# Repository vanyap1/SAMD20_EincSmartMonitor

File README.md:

# SAMD20_EinkSmartMonitor
Atmel SAMD20E17 mcu based EINK smart monitor with LORA module

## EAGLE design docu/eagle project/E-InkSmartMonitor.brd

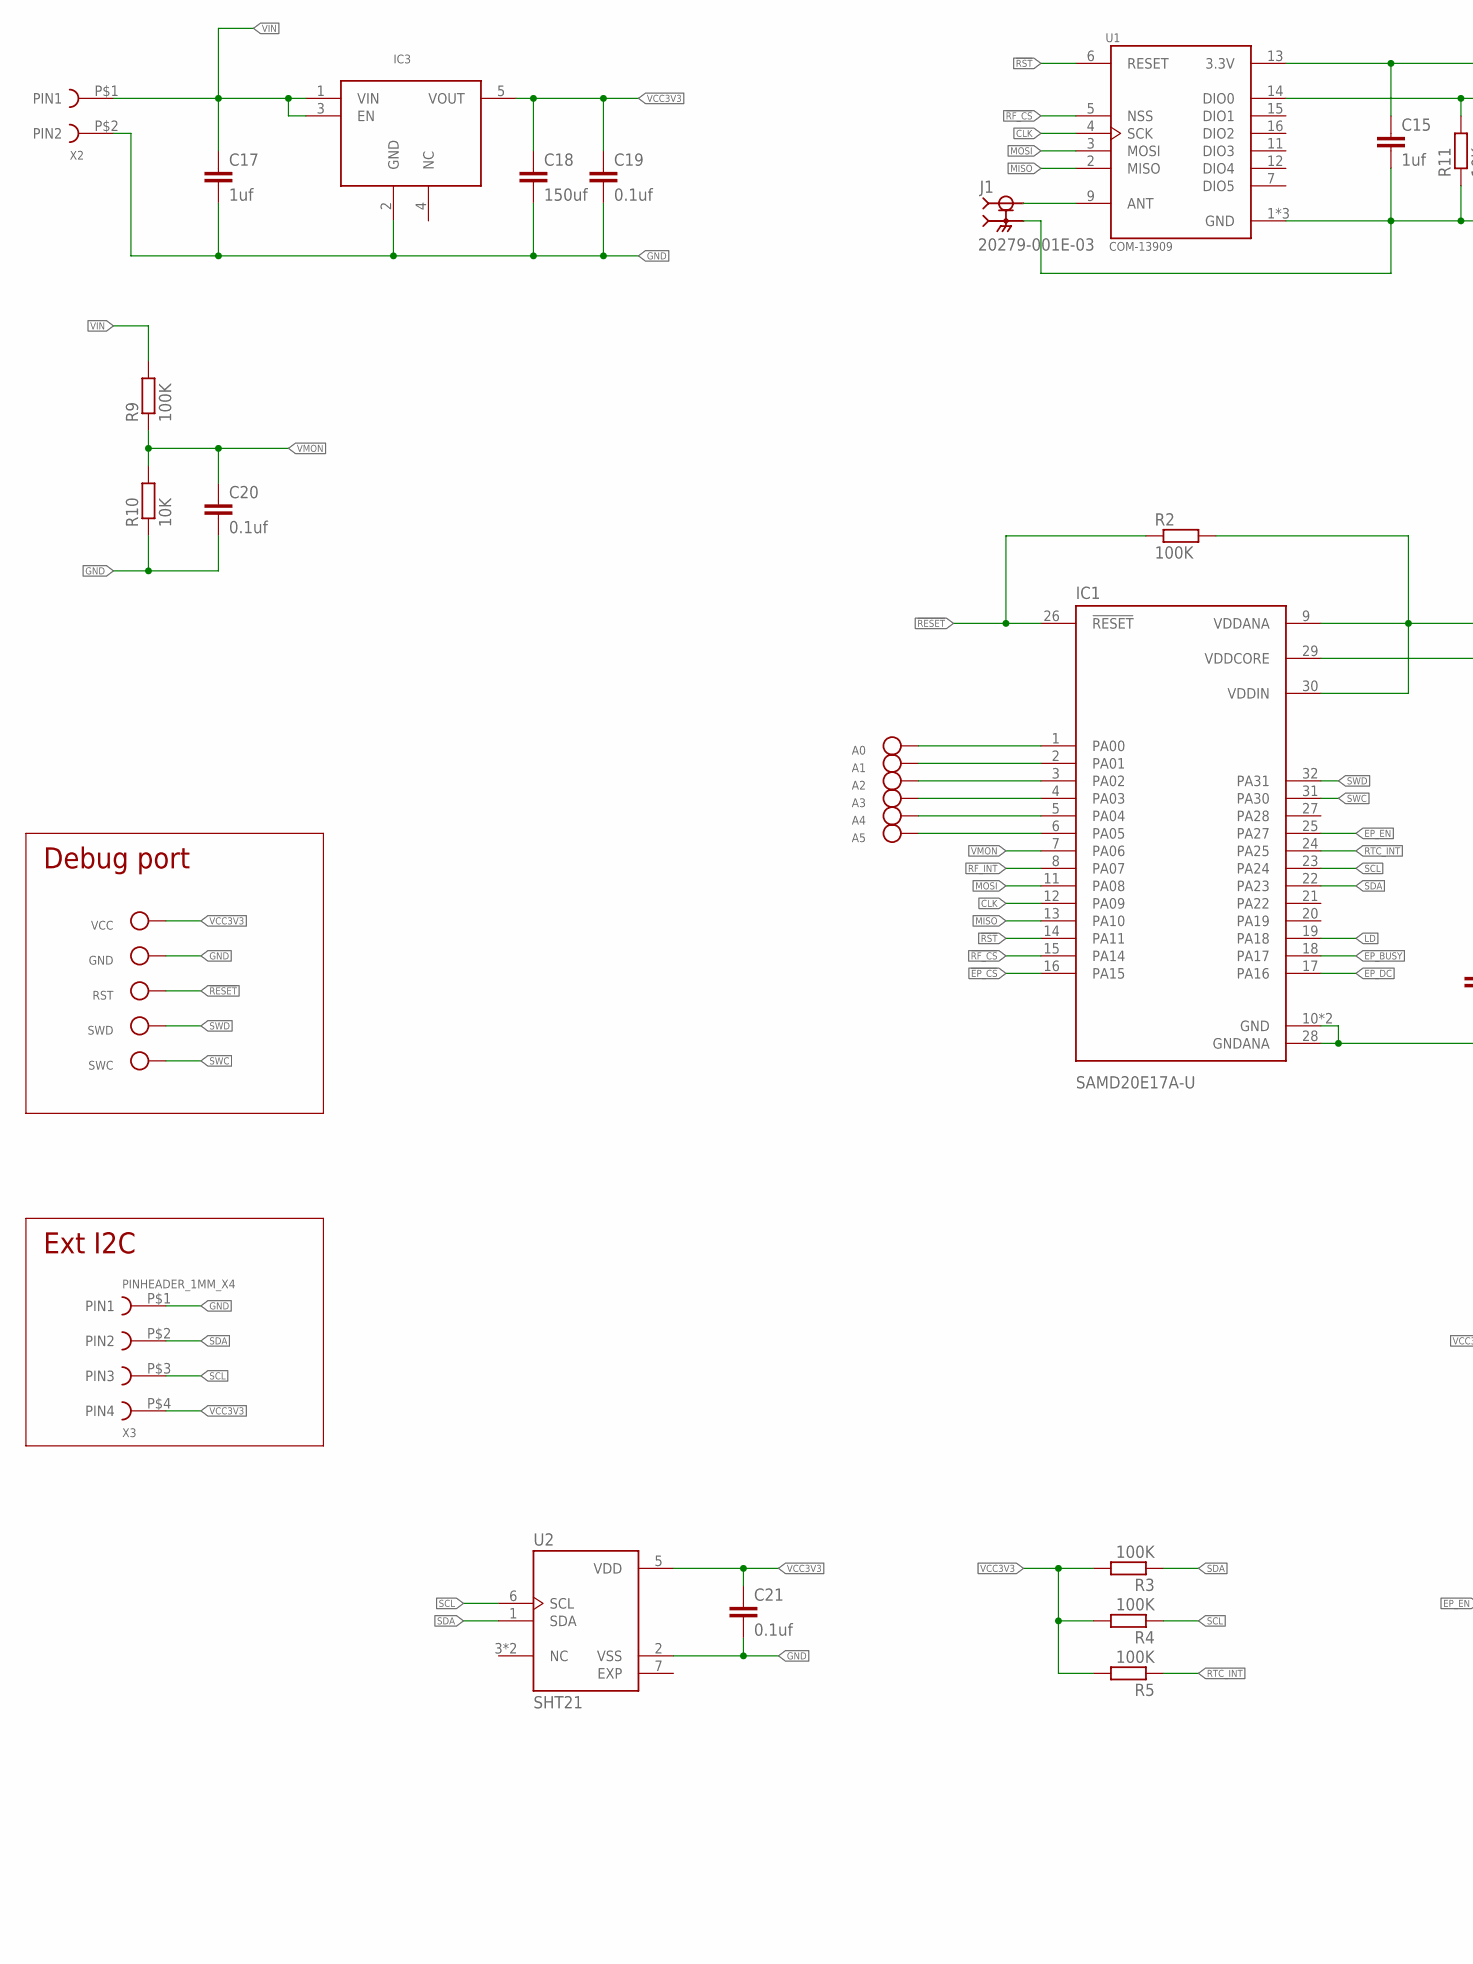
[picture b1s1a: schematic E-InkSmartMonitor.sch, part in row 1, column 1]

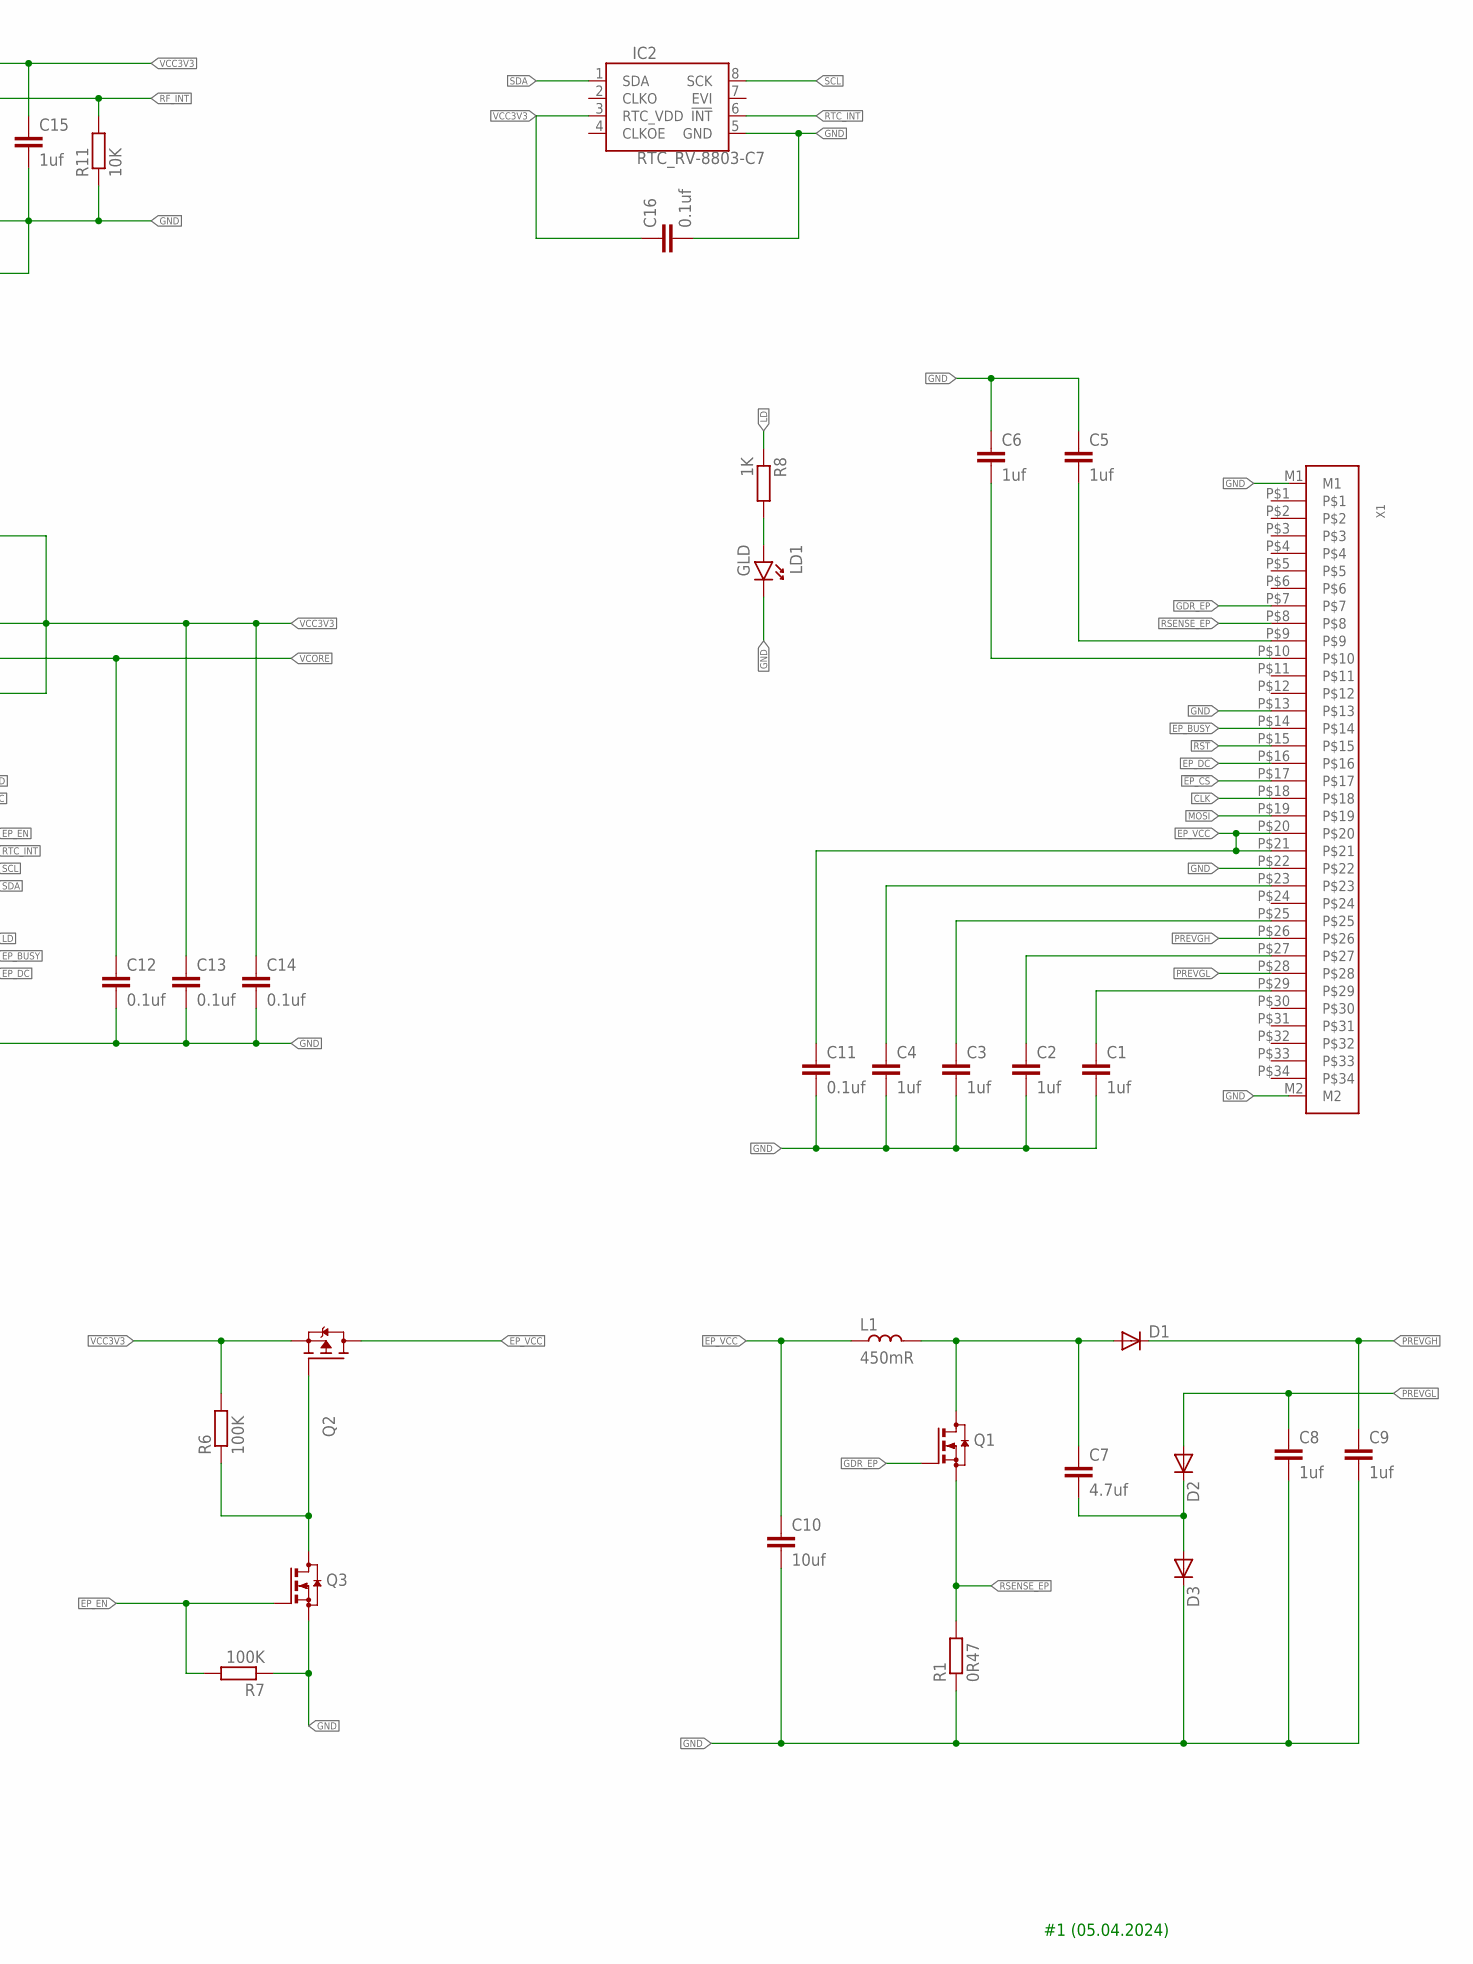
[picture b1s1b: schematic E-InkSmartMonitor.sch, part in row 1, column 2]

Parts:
A0, A1, A2, A3, A4, A5: TEST_POINT_D2MM; TP
C1, C2, C3, C4, C5, C6, C8, C9, C15, C17: 1uf; 0805
C7: 4.7uf; 0805
C10: 10uf; 0805
C11, C12, C13, C14, C16, C19, C20, C21: 0.1uf; 0603
C18: 150uf; 0805
D1, D2, D3: DIODE-SOD323-R; SOD323-R
GND: TEST_POINT_D2MM; TP
IC1: SAMD20E17A-U; MLF32-TH
IC2: RTC_RV-8803-C7; C7_RTC
IC3: LDO_3.3V_SOT23(5); SOT-23(5)
J1: 20279-001E-03; IPEX_20279-001E-03
L1: 450mR; 3232
LD1: GLD; 0603_P
Q1, Q3: BSS123SOT-23-3; SOT-23(3)
Q2: P_CH_SOT23SOT-23-3; SOT-23(3)
R1: 0R47; 0603
R2, R3, R4, R5, R6, R7, R9: 100K; 0603
R8: 1K; 0603
R10, R11: 10K; 0603
RST: TEST_POINT_D2MM; TP
SWC: TEST_POINT_D2MM; TP
SWD: TEST_POINT_D2MM; TP
U1: COM-13909; MOD_COM-13909
U2: SHT21; XDCR_SHT21
VCC: TEST_POINT_D2MM; TP
X1: FFC_3405EINK
X2: PINHEADER_1MM_X22X_1MM_PIN; PIN_1MM_X2
X3: PINHEADER_1MM_X4; PIN_1MM_X4

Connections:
!EP_CS: IC1.16 (PA15), X1.P$17
!RESET: IC1.26 (!RESET), R2.1, RST.P$1
!RF_CS: IC1.15 (PA14), U1.5 (NSS)
CLK: IC1.12 (PA09), U1.4 (SCK), X1.P$18
EP_BUSY: IC1.18 (PA17), X1.P$14
EP_DC: IC1.17 (PA16), X1.P$16
EP_EN: IC1.25 (PA27), Q3.1 (G), R7.2
EP_VCC: C10.1, C11.1, L1.M (1), Q2.3 (D), X1.P$20, X1.P$21
GDR_EP: Q1.1 (G), X1.P$7
GND: C1.2, C2.2, C3.2, C4.2, C5.1, C6.1, C8.2, C9.2, C10.2, C11.2, C12.2, C13.2, C14.2, C15.2, C16.2, C17.2, C18.2, C19.2, C20.2, C21.2, D3.C, GND.P$1, IC1.10 (GND), IC1.28 (GNDANA), IC1.TH (GND), IC2.5 (GND), IC3.2 (GND), J1.2 (GND), J1.3 (GND), LD1.1 (K), Q3.2 (S), R1.1, R7.1, R10.1, R11.1, U1.1 (GND), U1.8 (GND), U1.10 (GND), U2.2 (VSS), X1.M1, X1.M2, X1.P$13, X1.P$22, X2.P$2 (PIN2), X3.P$1 (PIN1)
LD: IC1.19 (PA18), R8.1
MISO: IC1.13 (PA10), U1.2 (MISO)
MOSI: IC1.11 (PA08), U1.3 (MOSI), X1.P$19
unnamed: J1.1 (SIG), U1.9 (ANT)
unnamed: Q2.1 (G), Q3.3 (D), R6.1
unnamed: C5.2, X1.P$9
unnamed: C6.2, X1.P$10
unnamed: C7.1, D1.A, L1.P (2), Q1.3 (D)
unnamed: LD1.2 (A), R8.2
unnamed: C7.2, D2.C, D3.A
unnamed: C4.1, X1.P$23
unnamed: C3.1, X1.P$25
unnamed: C2.1, X1.P$27
unnamed: C1.1, X1.P$29
PA00: A0.P$1, IC1.1 (PA00)
PA01: A1.P$1, IC1.2 (PA01)
PA02: A2.P$1, IC1.3 (PA02)
PA03: A3.P$1, IC1.4 (PA03)
PA04: A4.P$1, IC1.5 (PA04)
PA05: A5.P$1, IC1.6 (PA05)
PREVGH: C9.1, D1.C, X1.P$26
PREVGL: C8.1, D2.A, X1.P$28
RF_INT: IC1.8 (PA07), R11.2, U1.14 (DIO0)
RSENSE_EP: Q1.2 (S), R1.2, X1.P$8
RTC_INT: IC1.24 (PA25), IC2.6 (!INT), R5.1
SCL: IC1.23 (PA24), IC2.8 (SCK), R4.1, U2.6 (SCL), X3.P$3 (PIN3)
SDA: IC1.22 (PA23), IC2.1 (SDA), R3.1, U2.1 (SDA), X3.P$2 (PIN2)
SWC: IC1.31 (PA30), SWC.P$1
SWD: IC1.32 (PA31), SWD.P$1
VCC3V3: C13.1, C14.1, C15.1, C16.1, C18.1, C19.1, C21.1, IC1.9 (VDDANA), IC1.30 (VDDIN), IC2.3 (RTC_VDD), IC3.5 (VOUT), Q2.2 (S), R2.2, R3.2, R4.2, R5.2, R6.2, U1.13 (3.3V), U2.5 (VDD), VCC.P$1, X3.P$4 (PIN4)
VCORE: C12.1, IC1.29 (VDDCORE)
VIN: C17.1, IC3.1 (VIN), IC3.3 (EN), R9.2, X2.P$1 (PIN1)
VMON: C20.1, IC1.7 (PA06), R9.1, R10.2

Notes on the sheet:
Debug port
Ext I2C
#1 (05.04.2024)

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
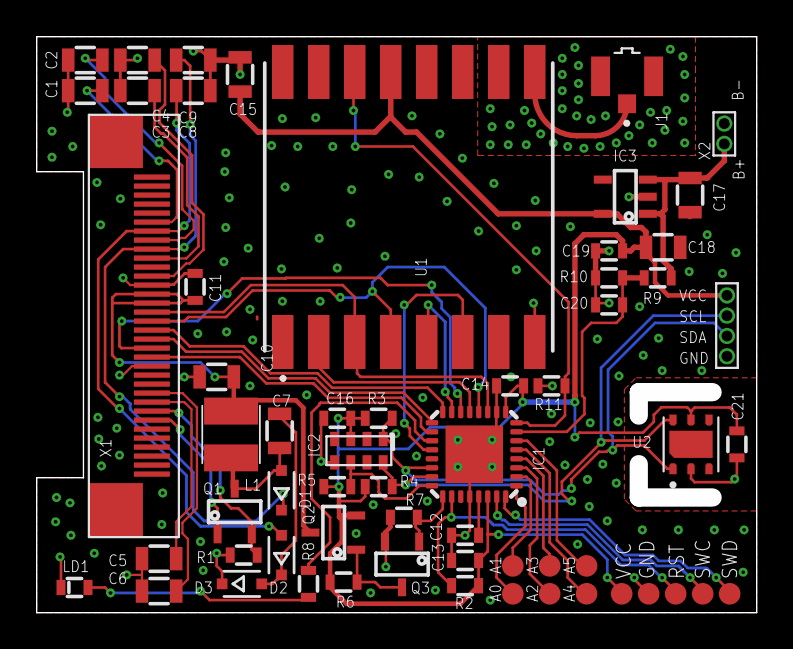
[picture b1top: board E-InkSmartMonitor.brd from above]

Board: 2 copper layers, 39.1 x 31.1 mm, 60 parts (0 on the bottom side), 45 nets.

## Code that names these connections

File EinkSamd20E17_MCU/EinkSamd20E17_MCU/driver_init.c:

/*
 * Code generated from Atmel Start.
 *
 * This file will be overwritten when reconfiguring your Atmel Start project.
 * Please copy examples or other code you want to keep to a separate file
 * to avoid losing it when reconfiguring.
 */

#include "driver_init.h"
#include <peripheral_clk_config.h>
#include <utils.h>
#include <hal_init.h>
#include <hpl_gclk_base.h>
#include <hpl_pm_base.h>

#include <hpl_adc_base.h>

struct spi_m_sync_descriptor SPI_0;

struct adc_sync_descriptor ADC_0;

struct i2c_m_sync_desc I2C_0;

void ADC_0_PORT_init(void)
{

	// Disable digital pin circuitry
	gpio_set_pin_direction(PA06, GPIO_DIRECTION_OFF);

	gpio_set_pin_function(PA06, PINMUX_PA06B_ADC_AIN6);
}

void ADC_0_CLOCK_init(void)
{
	_pm_enable_bus_clock(PM_BUS_APBC, ADC);
	_gclk_enable_channel(ADC_GCLK_ID, CONF_GCLK_ADC_SRC);
}

void ADC_0_init(void)
{
	ADC_0_CLOCK_init();
	ADC_0_PORT_init();
	adc_sync_init(&ADC_0, ADC, (void *)NULL);
}

void EXTERNAL_IRQ_0_init(void)
{
	_gclk_enable_channel(EIC_GCLK_ID, CONF_GCLK_EIC_SRC);

	// Set pin direction to input
	gpio_set_pin_direction(RF_INT, GPIO_DIRECTION_IN);

	gpio_set_pin_pull_mode(RF_INT,
	                       // <y> Pull configuration
	                       // <id> pad_pull_config
	                       // <GPIO_PULL_OFF"> Off
	                       // <GPIO_PULL_UP"> Pull-up
	                       // <GPIO_PULL_DOWN"> Pull-down
	                       GPIO_PULL_OFF);

	gpio_set_pin_function(RF_INT, PINMUX_PA07A_EIC_EXTINT7);

	// Set pin direction to input
	gpio_set_pin_direction(RTC_INT, GPIO_DIRECTION_IN);

	gpio_set_pin_pull_mode(RTC_INT,
	                       // <y> Pull configuration
	                       // <id> pad_pull_config
	                       // <GPIO_PULL_OFF"> Off
	                       // <GPIO_PULL_UP"> Pull-up
	                       // <GPIO_PULL_DOWN"> Pull-down
	                       GPIO_PULL_OFF);

	gpio_set_pin_function(RTC_INT, PINMUX_PA25A_EIC_EXTINT13);

	ext_irq_init();
}

void SPI_0_PORT_init(void)
{

	gpio_set_pin_level(PA08,
	                   // <y> Initial level
	                   // <id> pad_initial_level
	                   // <false"> Low
	                   // <true"> High
	                   false);

	// Set pin direction to output
	gpio_set_pin_direction(PA08, GPIO_DIRECTION_OUT);

	gpio_set_pin_function(PA08, PINMUX_PA08C_SERCOM0_PAD0);

	gpio_set_pin_level(PA09,
	                   // <y> Initial level
	                   // <id> pad_initial_level
	                   // <false"> Low
	                   // <true"> High
	                   false);

	// Set pin direction to output
	gpio_set_pin_direction(PA09, GPIO_DIRECTION_OUT);

	gpio_set_pin_function(PA09, PINMUX_PA09C_SERCOM0_PAD1);

	// Set pin direction to input
	gpio_set_pin_direction(PA10, GPIO_DIRECTION_IN);

	gpio_set_pin_pull_mode(PA10,
	                       // <y> Pull configuration
	                       // <id> pad_pull_config
	                       // <GPIO_PULL_OFF"> Off
	                       // <GPIO_PULL_UP"> Pull-up
	                       // <GPIO_PULL_DOWN"> Pull-down
	                       GPIO_PULL_OFF);

	gpio_set_pin_function(PA10, PINMUX_PA10C_SERCOM0_PAD2);
}

void SPI_0_CLOCK_init(void)
{
	_pm_enable_bus_clock(PM_BUS_APBC, SERCOM0);
	_gclk_enable_channel(SERCOM0_GCLK_ID_CORE, CONF_GCLK_SERCOM0_CORE_SRC);
}

void SPI_0_init(void)
{
	SPI_0_CLOCK_init();
	spi_m_sync_init(&SPI_0, SERCOM0);
	SPI_0_PORT_init();
}

void I2C_0_PORT_init(void)
{

	gpio_set_pin_pull_mode(PA22,
	                       // <y> Pull configuration
	                       // <id> pad_pull_config
	                       // <GPIO_PULL_OFF"> Off
	                       // <GPIO_PULL_UP"> Pull-up
	                       // <GPIO_PULL_DOWN"> Pull-down
	                       GPIO_PULL_OFF);

	gpio_set_pin_function(PA22, PINMUX_PA22C_SERCOM3_PAD0);

	gpio_set_pin_pull_mode(PA23,
	                       // <y> Pull configuration
	                       // <id> pad_pull_config
	                       // <GPIO_PULL_OFF"> Off
	                       // <GPIO_PULL_UP"> Pull-up
	                       // <GPIO_PULL_DOWN"> Pull-down
	                       GPIO_PULL_OFF);

	gpio_set_pin_function(PA23, PINMUX_PA23C_SERCOM3_PAD1);
}

void I2C_0_CLOCK_init(void)
{
	_pm_enable_bus_clock(PM_BUS_APBC, SERCOM3);
	_gclk_enable_channel(SERCOM3_GCLK_ID_CORE, CONF_GCLK_SERCOM3_CORE_SRC);
	_gclk_enable_channel(SERCOM3_GCLK_ID_SLOW, CONF_GCLK_SERCOM3_SLOW_SRC);
}

void I2C_0_init(void)
{
	I2C_0_CLOCK_init();
	i2c_m_sync_init(&I2C_0, SERCOM3);
	I2C_0_PORT_init();
}

void delay_driver_init(void)
{
	delay_init(SysTick);
}

void system_init(void)
{
	init_mcu();

	// GPIO on PA14

	gpio_set_pin_level(RF_CS,
	                   // <y> Initial level
	                   // <id> pad_initial_level
	                   // <false"> Low
	                   // <true"> High
	                   true);

	// Set pin direction to output
	gpio_set_pin_direction(RF_CS, GPIO_DIRECTION_OUT);

	gpio_set_pin_function(RF_CS, GPIO_PIN_FUNCTION_OFF);

	// GPIO on PA15

	gpio_set_pin_level(EP_CS,
	                   // <y> Initial level
	                   // <id> pad_initial_level
	                   // <false"> Low
	                   // <true"> High
	                   true);

	// Set pin direction to output
	gpio_set_pin_direction(EP_CS, GPIO_DIRECTION_OUT);

	gpio_set_pin_function(EP_CS, GPIO_PIN_FUNCTION_OFF);

	// GPIO on PA16

	gpio_set_pin_level(EP_CMD,
	                   // <y> Initial level
	                   // <id> pad_initial_level
	                   // <false"> Low
	                   // <true"> High
	                   true);

	// Set pin direction to output
	gpio_set_pin_direction(EP_CMD, GPIO_DIRECTION_OUT);

	gpio_set_pin_function(EP_CMD, GPIO_PIN_FUNCTION_OFF);

	// GPIO on PA17

	// Set pin direction to input
	gpio_set_pin_direction(EP_BUSY, GPIO_DIRECTION_IN);

	gpio_set_pin_pull_mode(EP_BUSY,
	                       // <y> Pull configuration
	                       // <id> pad_pull_config
	                       // <GPIO_PULL_OFF"> Off
	                       // <GPIO_PULL_UP"> Pull-up
	                       // <GPIO_PULL_DOWN"> Pull-down
	                       GPIO_PULL_UP);

	gpio_set_pin_function(EP_BUSY, GPIO_PIN_FUNCTION_OFF);

	// GPIO on PA18

	gpio_set_pin_level(GLD,
	                   // <y> Initial level
	                   // <id> pad_initial_level
	                   // <false"> Low
	                   // <true"> High
	                   false);

	// Set pin direction to output
	gpio_set_pin_direction(GLD, GPIO_DIRECTION_OUT);

	gpio_set_pin_function(GLD, GPIO_PIN_FUNCTION_OFF);

	// GPIO on PA27

	gpio_set_pin_level(EP_EN,
	                   // <y> Initial level
	                   // <id> pad_initial_level
	                   // <false"> Low
	                   // <true"> High
	                   true);

	// Set pin direction to output
	gpio_set_pin_direction(EP_EN, GPIO_DIRECTION_OUT);

	gpio_set_pin_function(EP_EN, GPIO_PIN_FUNCTION_OFF);

	ADC_0_init();
	EXTERNAL_IRQ_0_init();

	SPI_0_init();

	I2C_0_init();

	delay_driver_init();
}

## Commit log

2024-04-24 project init
2024-04-24 standby mode
2024-04-25 added pictures
2024-04-27 added real data drawing
2024-04-28 intermediad commit
2024-04-30 added 3d model for 1.54 inch screen
2024-04-30 added some changes and project template
